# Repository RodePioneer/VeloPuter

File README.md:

# VeloPuter
This repository contains the development of both the Arduino based hardware and the software for a Velomobile board computer.

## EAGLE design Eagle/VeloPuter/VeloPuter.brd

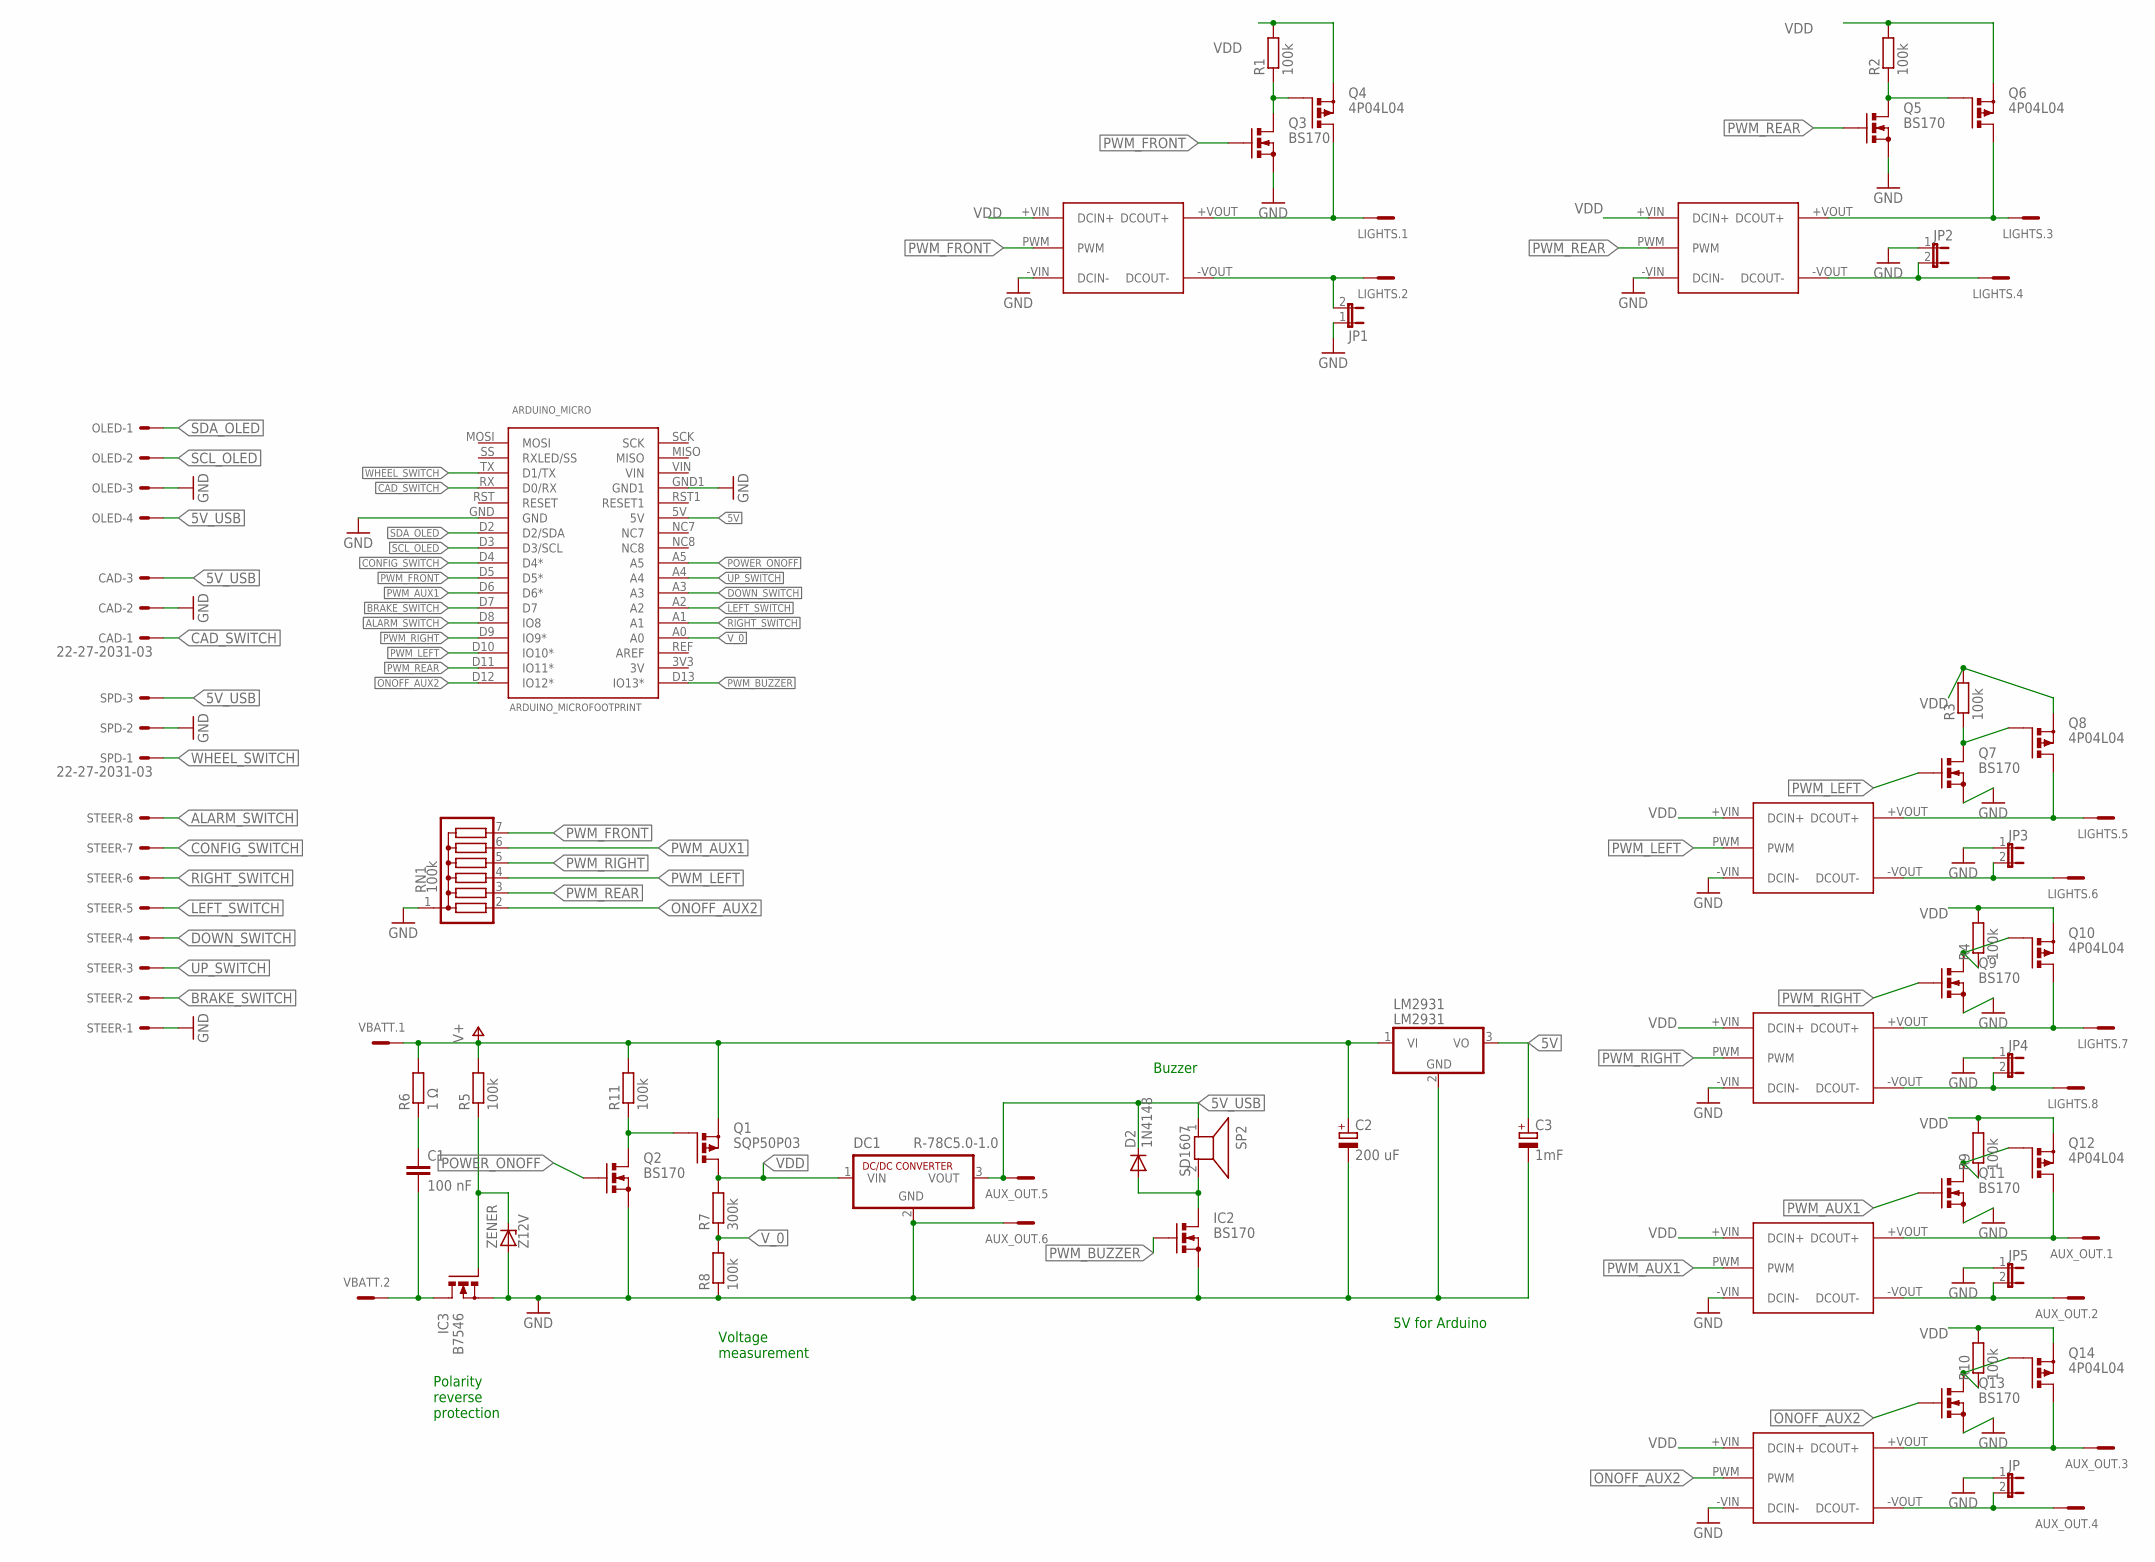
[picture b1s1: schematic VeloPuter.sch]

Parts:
ARDUINO_MICRO: ARDUINO_MICROFOOTPRINT; ARDUINO-MICRO
AUX_OUT: Aux; MCV6
BRAKE: LDD-L
C1: 100 nF; C2.5-3
C2: 200 uF; E5-10,5
C3: 1mF; E5-10,5
CAD: 22-27-2031-03; 6410-03
D2: 1N4148; DO35-7
DC1: R-78C5.0-1.0; SIP3
IC2: BS170; SOT54E
IC3: B7546; TO220BV
JP, JP1, JP2, JP3, JP4, JP5: JP1
LIGHTS: Lights; MCV8
LM2931: LM2931; TO220V
OLED: 22-27-2041-04; 6410-04
Q1: SQP50P03; TO220BV
Q2, Q3, Q5, Q7, Q9, Q11, Q13: BS170; SOT54E
Q4, Q6, Q8, Q10, Q12, Q14: 4P04L04; TO220BV
R1, R2, R3, R4, R5, R8, R9, R10, R11: 100k; 0207/7
R6: 1 Ω; 0207/7
R7: 300k; 0207/7
RN1: 100k; SIL7
SP2: SD1607; AL60P
SPD: 22-27-2031-03; 6410-03
STEER: 22-27-2081-08; 6410-08
U$1, U$2, U$3, U$4, U$5: LDD-L
VBATT: VBatt; MCV2
ZENER: Z12V; DO34Z7

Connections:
5V: ARDUINO_MICRO.5V, C3.+, LM2931.3 (VO)
5V_USB: AUX_OUT.5, CAD.3, D2.C, DC1.3 (VOUT), OLED.4, SP2.1, SPD.3
ALARM_SWITCH: ARDUINO_MICRO.D8 (IO8), STEER.8
AUX1+: AUX_OUT.1, Q12.D, U$5.+VOUT (DCOUT+)
AUX1-: AUX_OUT.2, JP5.2, U$5.-VOUT (DCOUT-)
AUX2+: AUX_OUT.3, Q14.D, U$1.+VOUT (DCOUT+)
AUX2-: AUX_OUT.4, JP.2, U$1.-VOUT (DCOUT-)
BRAKE_SWITCH: ARDUINO_MICRO.D7, STEER.2
CAD_SWITCH: ARDUINO_MICRO.RX (D0/RX), CAD.1
CONFIG_SWITCH: ARDUINO_MICRO.D4 (D4*), STEER.7
DOWN_SWITCH: ARDUINO_MICRO.A3, STEER.4
FRONT+: LIGHTS.1, Q4.D, U$4.+VOUT (DCOUT+)
FRONT-: JP1.2, LIGHTS.2, U$4.-VOUT (DCOUT-)
GND: ARDUINO_MICRO.GND, ARDUINO_MICRO.GND1, AUX_OUT.6, BRAKE.-VIN (DCIN-), C2.-, C3.-, CAD.2, DC1.2 (GND), IC2.S, IC3.S, JP.1, JP1.1, JP2.1, JP3.1, JP4.1, JP5.1, LM2931.2 (GND), OLED.3, Q2.S, Q3.S, Q5.S, Q7.S, Q9.S, Q11.S, Q13.S, R8.1, RN1.1, SPD.2, STEER.1, U$1.-VIN (DCIN-), U$2.-VIN (DCIN-), U$3.-VIN (DCIN-), U$4.-VIN (DCIN-), U$5.-VIN (DCIN-), ZENER.A
LEFT+: LIGHTS.5, Q8.D, U$2.+VOUT (DCOUT+)
LEFT-: JP3.2, LIGHTS.6, U$2.-VOUT (DCOUT-)
LEFT_SWITCH: ARDUINO_MICRO.A2, STEER.5
unnamed: C1.1, R6.1
unnamed: IC3.G, R5.1, ZENER.C
unnamed: D2.A, IC2.D, SP2.2
unnamed: Q1.G, Q2.D, R11.1
unnamed: Q3.D, Q4.G, R1.1
unnamed: Q5.D, Q6.G, R2.1
unnamed: Q7.D, Q8.G, R3.1
unnamed: Q9.D, Q10.G, R4.1
unnamed: Q11.D, Q12.G, R9.1
unnamed: Q13.D, Q14.G, R10.1
ONOFF_AUX2: ARDUINO_MICRO.D12 (IO12*), Q13.G, RN1.2, U$1.PWM
POWER_ONOFF: ARDUINO_MICRO.A5, Q2.G
PWM_AUX1: ARDUINO_MICRO.D6 (D6*), Q11.G, RN1.6, U$5.PWM
PWM_BUZZER: ARDUINO_MICRO.D13 (IO13*), IC2.G
PWM_FRONT: ARDUINO_MICRO.D5 (D5*), Q3.G, RN1.7, U$4.PWM
PWM_LEFT: ARDUINO_MICRO.D10 (IO10*), Q7.G, RN1.4, U$2.PWM
PWM_REAR: ARDUINO_MICRO.D11 (IO11*), BRAKE.PWM, Q5.G, RN1.3
PWM_RIGHT: ARDUINO_MICRO.D9 (IO9*), Q9.G, RN1.5, U$3.PWM
REAR+: BRAKE.+VOUT (DCOUT+), LIGHTS.3, Q6.D
REAR-: BRAKE.-VOUT (DCOUT-), JP2.2, LIGHTS.4
RIGHT+: LIGHTS.7, Q10.D, U$3.+VOUT (DCOUT+)
RIGHT-: JP4.2, LIGHTS.8, U$3.-VOUT (DCOUT-)
RIGHT_SWITCH: ARDUINO_MICRO.A1, STEER.6
SCL_OLED: ARDUINO_MICRO.D3 (D3/SCL), OLED.2
SDA_OLED: ARDUINO_MICRO.D2 (D2/SDA), OLED.1
UP_SWITCH: ARDUINO_MICRO.A4, STEER.3
V+: C2.+, LM2931.1 (VI), Q1.S, R5.2, R6.2, R11.2, VBATT.1
V-: C1.2, IC3.D, VBATT.2
VDD: BRAKE.+VIN (DCIN+), DC1.1 (VIN), Q1.D, Q4.S, Q6.S, Q8.S, Q10.S, Q12.S, Q14.S, R1.2, R2.2, R3.2, R4.2, R7.2, R9.2, R10.2, U$1.+VIN (DCIN+), U$2.+VIN (DCIN+), U$3.+VIN (DCIN+), U$4.+VIN (DCIN+), U$5.+VIN (DCIN+)
V_0: ARDUINO_MICRO.A0, R7.1, R8.2
WHEEL_SWITCH: ARDUINO_MICRO.TX (D1/TX), SPD.1

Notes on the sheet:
Polarity reverse protection
Voltage measurement
5V for Arduino
Buzzer

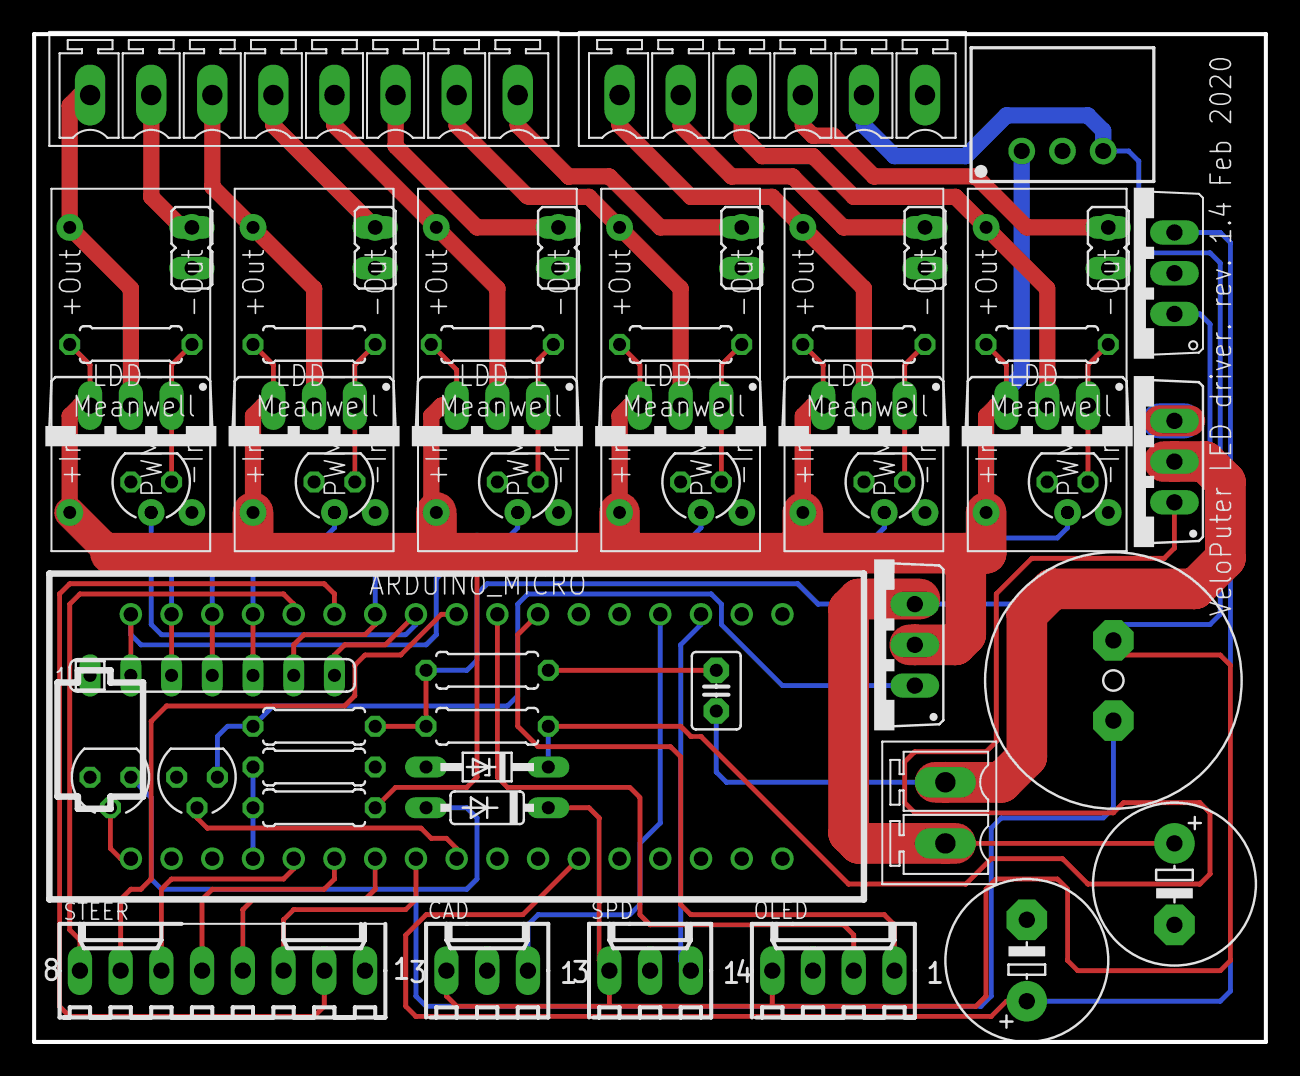
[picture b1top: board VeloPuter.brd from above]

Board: 2 copper layers, 76.8 x 62.9 mm, 56 parts (0 on the bottom side), 48 nets.

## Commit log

2016-01-25 Initial commit of the project until now. This includes a functionional -though not complete- arduino sketch and eagle PCB-design files.
    Arduini libraries are not included.
2016-01-25 Partial redesign due to insights from the first builds - VDD of the oled now goes to the 5V not Vbatt. - Larger capacitor for C2. - LM2931 replaced by a TO220 (need new layout for this) - Brake handl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
2016-01-28 Putting files back...
2016-01-30 Added pulldown resistors for the LDD700 PWM inputs. Without these resistors the LED's would flash brightly before the arduino kicks in.
2016-01-30 Added files to the ignore list.
2016-02-03 Got the spedometer and the cadense working.
2016-02-08 Switched spd and cad pins. Switched switchHeadUpPin and switchHeadDownPin Reduced the number of blinks to 7 Added splash screen Updated the LED intensity of the low setting for the head light 8->16 U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
2016-02-13 Updated the display of the battery voltage: it now shows the cell voltage for one cell and estimates of we have 2,3 or 4 cells on board.
    The wheel and cadence sensors are bedounced differently.
2016-02-15 Development backup: - implemented a timed interupt. - sleep mode updates
    seems still a little bit buggy....
2016-02-16 improvements to the archrtecture: in interupts should freez no more.
2016-05-11 new board layout
    has to be checked. Pin changes NOT documented
2016-06-21 Version of the Veloputer PCB as made as version 1.2 (number of the PCB).
    This version is uploaded to seeedstudio.com on 2016-02-21.
2017-01-07 Code to go with the PCB version 1.2. Suitable for Strada.
2017-01-09 Update: setting zoomer to off during alarm blinking
2017-01-17 Bugfix: blinkers could stay on during operation.
2017-01-18 Bill of Materials added
2017-03-21 Updates. Added brake light, config for oled intesity and alarmlights button
2017-03-27 Got rid of Timer1. Changed the implementation of the draw routine. It now runs directly from the loop.
2017-05-31 Updates: option to disable battery management. Also: estimation of the current gear (does not yet include multple chainrings / slumpf up front
2017-09-30 Versie Intercitybike DF
2017-10-01 Add preprocessor constant for DF
    Change default cassette gear string to "-" (might be in numeric font)
    Rear gear display needed a scaling with the ration of front and read
    wheel sizes
    Add correct wheel sizes for DF
2017-10-02 Correct ratio for gear calculation Set aux led to 0 for all intensities in ICB_DF (not connected).
2017-10-02 Updates to aux led for ICB_DF and gears to byte to save memory
2017-10-02 Set real tooth counts for 11-32 cassette in DF
2017-10-23 Merged the additions by Maarten manually
2017-11-30 Use integer values, avoid divisions and round as needed.
2017-11-30 Simplify battery voltage to percentage conversion.
2017-12-20 Lots of changes: - Switched battery management back to LiPo. This has to be updated soon. - setTeethOnCassette is back to float. This is in order to handle the Slumpf better. Now printing the rounded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
2018-01-04 Started working on the PCB again. Adding swtichoff of the ALL Ldd's. Also: adding a 6th LDDd.
2018-01-08 - Added alternative components for the LDDs to be placed at the same positions - Added 5V USB - Added overall Power off - Added 6th LDD/switch (was 5) -> possible also for buzzer. Note that a key for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
2018-01-09 Finished placing the components. Next: routing the connections.
2018-01-11 Routing done. Next: tripple check everything (such as pinning, lost connections, spacings, design rules etc, etc
2018-01-18 Allow selection of battery-type via precompiler constant.
2018-01-20 Move configuration to a separate header file, and use a script (python) to generate that header.
2018-01-20 Make sure that updateBattery() function uses global variable. Otherwise the display will always show 4.20 V.
2018-01-20 Minor layout change
2018-01-20 Cleanup Update.ino - commented code - erronour #IF #ELSE
2018-01-21 Use floats for the cassette teeth. Add initial draft for the use cases.
2018-05-12 Fix for interference between timeout of brake light and rear light intensity.
2018-08-26 Updated the voltage/capacity table for LiFePO4 batteries.
2019-08-13 Added brakelight timeout. Stops after configured time and also stopns when the bike stopped
2019-08-16 Made aux flash during fog-rear light conditions specific to QuattroVelo only.
    DF and other three-wheelers don't have an AUX light.
2019-11-18 Clean-up of the configuration header, remove cassette settings. Add option to configure the dimmed intensity.
2019-12-23 Update configuration script, allow to set the middle intensity of the head lights. Constants is modified to use the same defaults as before, if you don't want to update the VeloPuter_Config.h file.
2019-12-23 Always run before committing.
2020-01-02 Add flash to fog-setting of rear LED.
    Adds logic to LED class, and uses it from update. Only for ICB_DF, but other
    flashes may benefit as well.
2020-01-26 fix typos
2020-02-01 Board updates
2020-04-04 Board version 1.4 Suitable for the QV with new headlights
2020-04-07 Backup commit.
2020-05-17 Splitting the update file into multiple ones for a better overview
2020-05-17 Refactoring.
    - deletion of unused code
    - Making the units the configs in config.h more human readable.
2020-05-24 Non-functional updates
    - More structuire according to SR
    - Code clean
    - Removed unused and commencted code
    - Added comments
    - Changed dis visuals for values when they are unknown.
2020-05-24 Added a file to the board design
2020-05-24 Code clean sleep (and a re-name for the setup)
2020-05-24 Ignore file
2020-05-24 Code cleaning sleep and battery watchdog.
2020-05-24 Removal of unused code. Restructuring the battery management.
2020-05-25 Backup: halfway creating a battery object.
2020-05-25 Battery voltage is now working.
2020-05-29 Updates on Battery/Power management. Also reduced fonts flash usage by using a smaller font.
2020-06-07 Added a delay timer to a Batter Color code change.
2020-06-07 Reworking LED settigns structure into a more simple structure. Work in progress. Backup commit.
2021-06-21 Minor chages. Backup commit.
2021-10-22 Updated comments and reformated the code. No functional changes to the code.
2021-10-22 Added xls with the desired lights functionality
2021-10-22 Updates to the power management. - Renames aux2Led to auxLed - Added a power state to the leds (this is to prevent the use of a global)\ - Limited the max intensity based on the battery level.
2021-10-22 Work in progress. Backup
2021-10-22 Basics of rework on the leds is working. Needs more work. Power management should be working but is not tested.
2021-10-22 Removed all the setLedMax and replaced it with a more sophistacted toggleMax. Now we do not need to keep track of the previous intensity for brake lights of indicators.
2021-10-22 Updated display code. Mainly debugging into enalbed and disabled.
2021-10-22 Working on the powermanagement. It now properly cycles though the power modes in a downward spiral to black....
2021-10-22 (auto)formated the code and minor constants changed.
2021-10-22 Fix:- error in display Fix:- Got powermanagement working.
2021-10-23 Lots of bug hunting. The new code seems a lot more mature and seems to work like intended. Basically it does the same as the old code but a bit more structured.
2021-10-23 cosmetics to the display and some paramter updates
2021-10-27 Added some todo's to the code.
2021-10-28 Added (fog) flashing brake light functionality.
    It flashes the rear light in all modes except low rear light more.
2021-10-28 Code cleaned UpdateRearLights.ino and added readable comments.
2021-10-28 Formatted some code properly
2021-10-30 Lots of updated comments, formatting and a fix in the order for the rear lights when sensors are active.
    (Something may still be fishy)
2022-07-05 Pins correctly set. Aux as a 2nd head light. Still a fraction too slow.
2022-07-05 Feature: Updated voltage calculation Fix: brake icon showed when the brakelight flashes without checking the brake handle. This is now fixed.
2022-07-08 Updated comments and removed unused lies.
2022-07-08 Bughunting the power issue. Backup commit.This at least works...
2022-07-08 Found the bug. Work around in place. Now make sure it also works as it should.....
2022-07-08 Cleaned the battery code. This is faster and more inline with Single Responsibility. Also all calculations are not not done at a high frequency.
2022-07-09 Fixed all (? How sure am I ?) bug. Only minor issues remain.
2022-07-09 Cleanup Leds
2022-07-10 Cleanup of the draw functions
2022-07-10 When disabeling battery monitoring we set the battery status to green so all functions are available.
2022-07-10 Trivial: remove empty lines and added comments
2022-07-10 Minor code optimization in battery and updated comments.
2022-07-10 Removed the battery status debugging voltage values.
2022-07-15 Fixed issue with not averaging the voltage pin mean. Added delay before battery management kicks in for safety reasons. Made the exclamation mark for low battery voltage smaller.
